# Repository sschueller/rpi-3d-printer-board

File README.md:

# Raspberry Pi 3D Printer Aux Board

This simple RPI board fits ontop of an RPI3+ and can supply it with power without requiring any external extras. It provides a few general features used in 3d printing and simplifies the wiring required. To control the fans, LEDs, relays etc. the https://plugins.octoprint.org/plugins/enclosure/ is recommended 

## Features
- 12V - 28V In
- 12V Out
- 5V Out
- 5V (Max 3A) power directly to Raspberry Pi
- Built in relay (NC and NO connetions)
- 4 x 12V fan connections with PWM and RPM
- Per fan selectable PWM (PWM0 or PWM1)
- 4 x Exposed GPIO (5,6,10,16) level shifted to 5V (Output Only) 
- LED indicator for relay
- USB Power Out port

## BOM

| Symbol  | Part  | Notes |
|---|---|---|
| M1A  | LM2596 | tuned to 5.1V (use 4 x 2.54m 2-pin header to connect)  |
| M2A  | LM2596 | tuned to 12V (use 4 x 2.54m 2-pin header to connect)  |
| U1  | SN74HCT245 | 20-SSOP (0,209", 5,30mm Width) |
| K1  | G6K-2F-Y (5V) | |
| D1  | 1206 SMD LED | |
| R1  | 1206 SMD 2.2k | |
| R2  | 1206 SMD 2.2k | |
| R3  | 1206 SMD 2.2k | |
| R4  | 1206 SMD 2.2k | |
| R5  | 1206 SMD 150 Ohm | |
| R6  | 1206 SMD 0 Ohm (bridge) | |
| P1  | RPI 2.54m 2x20-pin female header | |
| J1  | 2-poin Phoenix Contact screw terminal 5.08mm | |
| J2  | 2.54mm 2x8-pin header | |
| J3  | Phoenix Contact 10x3.81mm Vertical | |
| J6  | 2510 2.54mm KF2510 3+1P | |
| J7  | 2510 2.54mm KF2510 3+1P | |
| J8  | 2510 2.54mm KF2510 3+1P | |
| J9  | 2510 2.54mm KF2510 3+1P | |
| J11 | USB Type A Female 4Pin Socket Connector For PCB - through hole | |
| J12 | 2.54mm 2-pin header | |

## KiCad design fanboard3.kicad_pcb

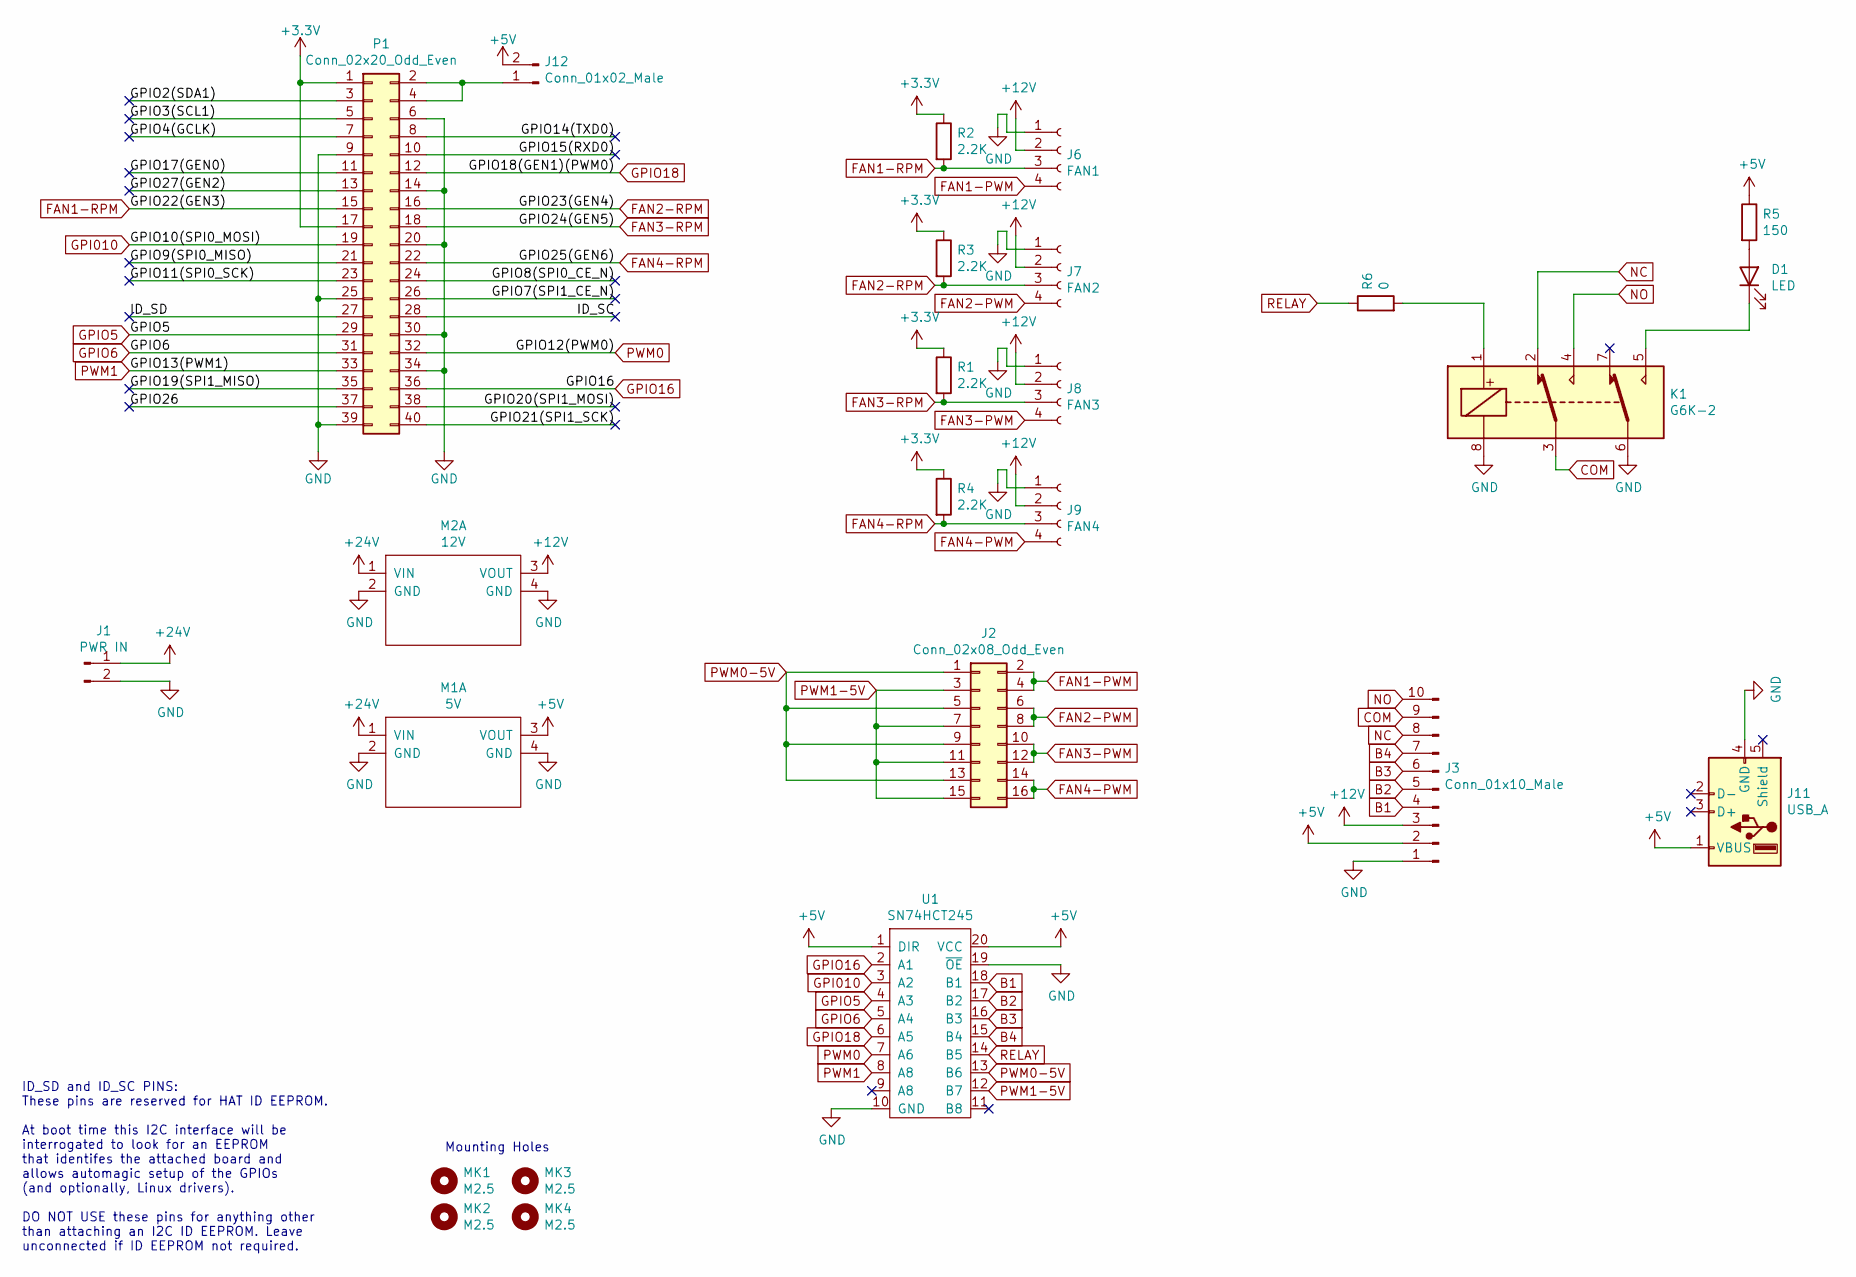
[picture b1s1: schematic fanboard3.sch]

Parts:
D1: LED; D_1206
J1: PWR IN; PhoenixContact_MC-G_02x5.08mm_Angled
J2: Conn_02x08_Odd_Even; Pin_Header_Straight_2x08_Pitch2.54mm
J3: Conn_01x10_Male; PhoenixContact_MCV-G_10x3.81mm_Vertical
J6: FAN1; Molex_KK-6410-04_04x2.54mm_Straight
J7: FAN2; Molex_KK-6410-04_04x2.54mm_Straight
J8: FAN3; Molex_KK-6410-04_04x2.54mm_Straight
J9: FAN4; Molex_KK-6410-04_04x2.54mm_Straight
J11: USB_A
J12: Conn_01x02_Male; Pin_Header_Straight_1x02_Pitch2.54mm
K1: G6K-2; Relay_DPDT_Omron_G6K-2F-Y
M1: 5V; buck-converter-module
M2: 12V; buck-converter-module
MK1, MK2, MK3, MK4: M2.5; MountingHole_2.7mm_M2.5
P1: Conn_02x20_Odd_Even; PinSocket_2x20_P2.54mm_Vertical
R1, R2, R3, R4: 2.2K; R_1210_HandSoldering
R5: 150; R_1210_HandSoldering
R6: 0; R_1210_HandSoldering
U1: SN74HCT245; SSOP-20_5.3x7.2mm_Pitch0.65mm

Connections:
+3V3: P1.1, P1.17, R1.1, R2.1, R3.1, R4.1
+5V: J3.2, J11.1 (VBUS), J12.2, M1.3 (VOUT), R5.1, U1.1 (DIR), U1.20 (VCC)
+12V: J3.3, J6.2, J7.2, J8.2, J9.2, M2.3 (VOUT)
+24V: J1.1, M1.1 (VIN), M2.1 (VIN)
/GPIO2(SDA1): P1.3
/GPIO3(SCL1): P1.5
/GPIO4(GCLK): P1.7
/GPIO7(SPI1_CE_N): P1.26
/GPIO8(SPI0_CE_N): P1.24
/GPIO9(SPI0_MISO): P1.21
/GPIO11(SPI0_SCK): P1.23
/GPIO14(TXD0): P1.8
/GPIO15(RXD0): P1.10
/GPIO17(GEN0): P1.11
/GPIO19(SPI1_MISO): P1.35
/GPIO20(SPI1_MOSI): P1.38
/GPIO21(SPI1_SCK): P1.40
/GPIO26: P1.37
/GPIO27(GEN2): P1.13
/ID_SC: P1.28
/ID_SD: P1.27
B1: J3.4, U1.18 (B1)
B2: J3.5, U1.17 (B2)
B3: J3.6, U1.16 (B3)
B4: J3.7, U1.15 (B4)
COM: J3.9, K1.3
FAN1-PWM: J2.2, J2.4, J6.4
FAN1-RPM: J6.3, P1.15, R2.2
FAN2-PWM: J2.6, J2.8, J7.4
FAN2-RPM: J7.3, P1.16, R3.2
FAN3-PWM: J2.10, J2.12, J8.4
FAN3-RPM: J8.3, P1.18, R1.2
FAN4-PWM: J2.14, J2.16, J9.4
FAN4-RPM: J9.3, P1.22, R4.2
GND: J1.2, J3.1, J6.1, J7.1, J8.1, J9.1, J11.4 (GND), K1.6, K1.8, M1.2 (GND), M1.4 (GND), M2.2 (GND), M2.4 (GND), P1.6, P1.9, P1.14, P1.20, P1.25, P1.30, P1.34, P1.39, U1.10 (GND), U1.19 (~OE)
GPI010: P1.19, U1.3 (A2)
GPIO5: P1.29, U1.4 (A3)
GPIO6: P1.31, U1.5 (A4)
GPIO16: P1.36, U1.2 (A1)
GPIO18: P1.12, U1.6 (A5)
NC: J3.8, K1.2
NO: J3.10, K1.4
unnamed: D1.1 (K), K1.5
unnamed: D1.2 (A), R5.2
unnamed: J12.1, P1.2, P1.4
unnamed: K1.1, R6.2
PWM0: P1.32, U1.7 (A6)
PWM0-5V: J2.1, J2.5, J2.9, J2.13, U1.13 (B6)
PWM1: P1.33, U1.8 (A8)
PWM1-5V: J2.3, J2.7, J2.11, J2.15, U1.12 (B7)
RELAY: R6.1, U1.14 (B5)

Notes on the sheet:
ID_SD and ID_SC PINS: These pins are reserved for HAT ID EEPROM. At boot time this I2C interface will be interrogated to look for an EEPROM that identifes the attached board and allows automagic setup of the GPIOs (and optionally, Linux drivers). DO NOT USE these pins for anything other than attach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
Mounting Holes

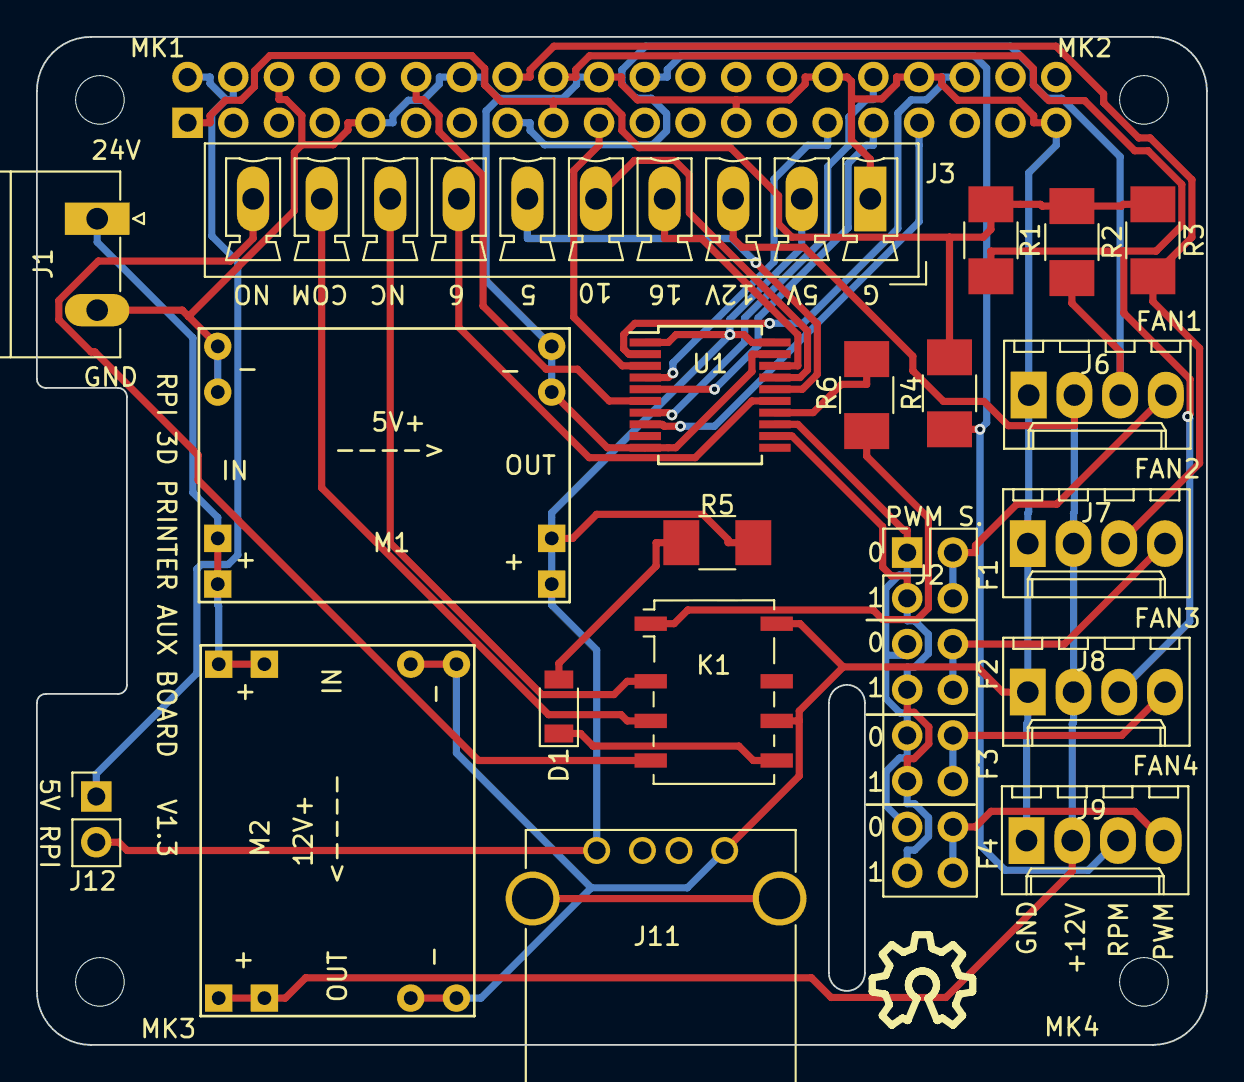
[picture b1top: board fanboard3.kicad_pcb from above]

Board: 2 copper layers, 65.0 x 56.0 mm, 25 parts (1 on the bottom side), 34 nets.

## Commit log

2021-09-17 added Volt meter and changed layout
2021-10-12 adjustments
2021-10-15 Add LICENSE
2021-10-15 Added CI
2021-10-15 Update .gitlab-ci.yml file
2021-10-16 WciW
2021-10-17 fix: Added Title to Readme
2021-10-17 chore(release): 1.0.0 [only cd]
    # 1.0.0 (2021-10-17)
    ### Bug Fixes
    * Added Title to Readme 6cb25be
2021-10-17 fix: CI
2021-10-17 chore(release): 1.0.1 [only cd]
    ## 1.0.1 (2021-10-17)
    ### Bug Fixes
    * CI 7c0ebf3
2021-11-07 Added photos
2021-11-07 BOM fixes
